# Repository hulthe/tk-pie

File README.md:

# Tk🥧
Alternatively: **tk-pie**, or **Test Keyboard Please IgnorE**.
A split keyboard design and firmware.

## Directory

### `/lib`
A rust library, and the bulk of the keyboard firmware implementation.
Written using the Embassy framework.

### `/left` and `/right`
Rust binaries, one for each half of the split keyboard.
Most of the actual logic is implemented in `/lib`.

### `/schematic`
KiCad schematics of the keyboard PCBs.

### `/case`
3d-printable files of the keyboard case and related plastics.

### `/editor`
A graphical program for configuring the keyboard layout. Work in progress.

## Firmware development

Required tools:
- Rust
- `probe-rs` for flashing the firmware. Follow instructions at https://probe.rs/
- [`flip-link`](https://github.com/knurling-rs/flip-link/)
- A debug probe of some kind, I recommend a [Pitaya-Link](https://github.com/makerdiary/pitaya-link)

To flash:
- plug in the probe,
- `cd` into either `left` or `right`
- `cargo run`

### Running tests
The keyboad library comes with some unit tests:
```
cargo test -p tk-pie --target x86_64-unknown-linux-gnu
```

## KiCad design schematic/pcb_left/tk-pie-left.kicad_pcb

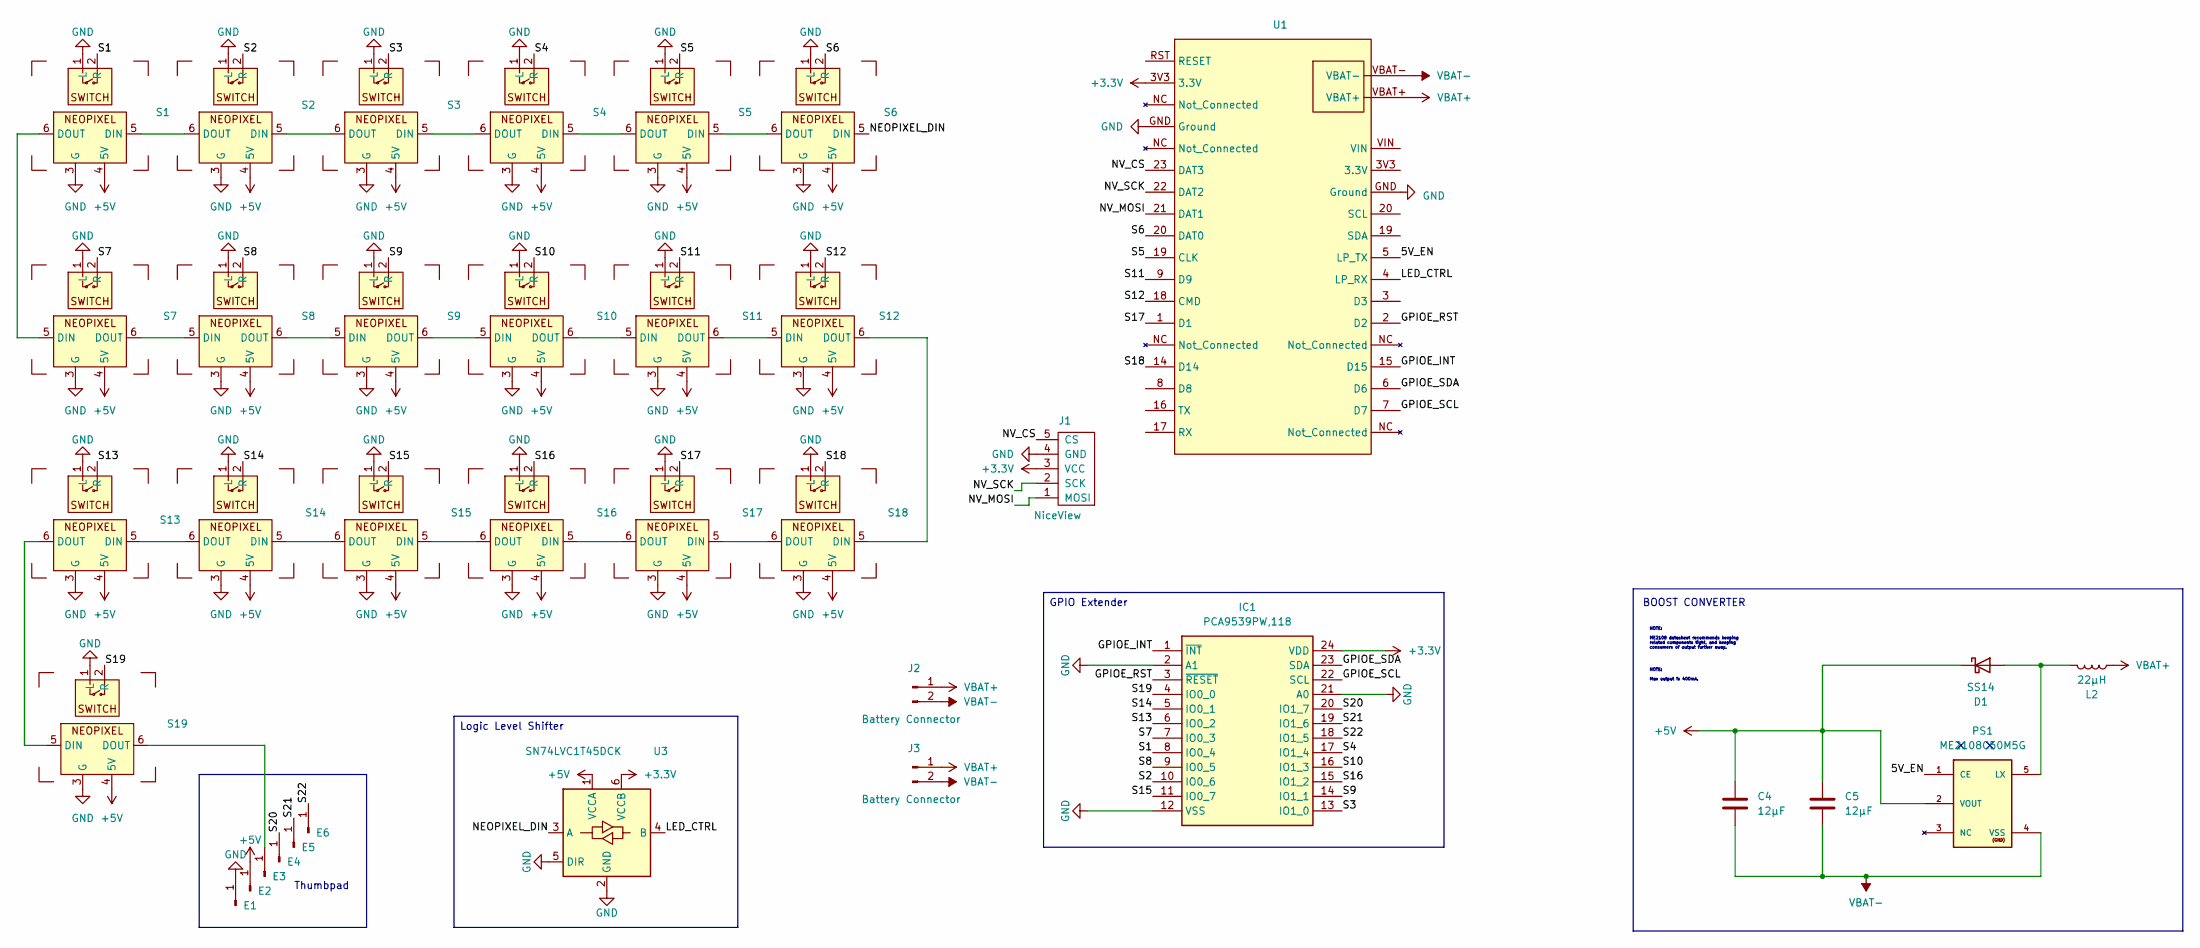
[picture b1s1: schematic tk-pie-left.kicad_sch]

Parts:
C4, C5: 12µF; C_1210_3225Metric_Pad1.33x2.70mm_HandSolder
D1: SS14; D_SMA
E1, E2, E3, E4, E5, E6: Conn_01x01_Pin; Pin0.9mm
IC1: PCA9539PW,118; SOP65P640X110-24N; Manufacturer_Part_Number PCA9539PW,118; Mouser Part Number 771-PCA9539PW-T
J1: NiceView; Nice!View Header
J2, J3: Battery Connector; JST_PH_S2B-PH-SM4-TB_1x02-1MP_P2.00mm_Horizontal
L2: 22µH; L_Cenker_CKCS5040
PS1: ME2108C50M5G; SOT-23-5
S1, S4, S5, S6, S13: MX_SW_SOCKET_LED
S2, S3, S14, S15, S16, S17, S18: MX_SW_SOCKET_LED
S7, S8, S9, S10, S11, S12, S19: MX_SW_SOCKET_RGB_REV; MX_SW_SOCKET_LED_REV
U1: DFR1075
U3: SN74LVC1T45DCK; SOT-363_SC-70-6_Handsoldering

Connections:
+3.3V: IC1.24 (VDD), J1.3 (VCC), U1.3V3 (3.3V), U3.6 (VCCB)
+5V: C4.1, C5.2, D1.1 (K), E2.1, PS1.2 (VOUT), S1.4 (5V), S2.4 (5V), S3.4 (5V), S4.4 (5V), S5.4 (5V), S6.4 (5V), S7.4 (5V), S8.4 (5V), S9.4 (5V), S10.4 (5V), S11.4 (5V), S12.4 (5V), S13.4 (5V), S14.4 (5V), S15.4 (5V), S16.4 (5V), S17.4 (5V), S18.4 (5V), S19.4 (5V), U3.1 (VCCA)
/5V_EN: PS1.1 (CE), U1.5 (LP_TX)
/ NV_CS: J1.5 (CS), U1.23 (DAT3)
/GPIOE_INT: IC1.1 (~INT), U1.15 (D15)
/GPIOE_RST: IC1.3 (~RESET), U1.2 (D2)
/GPIOE_SCL: IC1.22 (SCL), U1.7 (D7)
/GPIOE_SDA: IC1.23 (SDA), U1.6 (D6)
/LED_CTRL: U1.4 (LP_RX), U3.4 (B)
/NEOPIXEL_DIN: S6.5 (DIN), U3.3 (A)
/NV_MOSI: J1.1 (MOSI), U1.21 (DAT1)
/NV_SCK: J1.2 (SCK), U1.22 (DAT2)
/S1: IC1.8 (IO0_4), S1.2 (R)
/S2: IC1.10 (IO0_6), S2.2 (R)
/S3: IC1.13 (IO1_0), S3.2 (R)
/S4: IC1.17 (IO1_4), S4.2 (R)
/S5: S5.2 (R), U1.19 (CLK)
/S6: S6.2 (R), U1.20 (DAT0)
/S7: IC1.7 (IO0_3), S7.2 (R)
/S8: IC1.9 (IO0_5), S8.2 (R)
/S9: IC1.14 (IO1_1), S9.2 (R)
/S10: IC1.16 (IO1_3), S10.2 (R)
/S11: S11.2 (R), U1.9 (D9)
/S12: S12.2 (R), U1.18 (CMD)
/S13: IC1.6 (IO0_2), S13.2 (R)
/S14: IC1.5 (IO0_1), S14.2 (R)
/S15: IC1.11 (IO0_7), S15.2 (R)
/S16: IC1.15 (IO1_2), S16.2 (R)
/S17: S17.2 (R), U1.1 (D1)
/S18: S18.2 (R), U1.14 (D14)
/S19: IC1.4 (IO0_0), S19.2 (R)
/S20: E4.1, IC1.20 (IO1_7)
/S21: E5.1, IC1.19 (IO1_6)
/S22: E6.1, IC1.18 (IO1_5)
GND: E1.1, IC1.2 (A1), IC1.12 (VSS), IC1.21 (A0), J1.4 (GND), S1.1 (L), S1.3 (G), S2.1 (L), S2.3 (G), S3.1 (L), S3.3 (G), S4.1 (L), S4.3 (G), S5.1 (L), S5.3 (G), S6.1 (L), S6.3 (G), S7.1 (L), S7.3 (G), S8.1 (L), S8.3 (G), S9.1 (L), S9.3 (G), S10.1 (L), S10.3 (G), S11.1 (L), S11.3 (G), S12.1 (L), S12.3 (G), S13.1 (L), S13.3 (G), S14.1 (L), S14.3 (G), S15.1 (L), S15.3 (G), S16.1 (L), S16.3 (G), S17.1 (L), S17.3 (G), S18.1 (L), S18.3 (G), S19.1 (L), S19.3 (G), U1.GND (Ground), U3.2 (GND), U3.5 (DIR)
unnamed: D1.2 (A), L2.2, PS1.5 (LX)
unnamed: E3.1, S19.6 (DOUT)
unnamed: S1.5 (DIN), S2.6 (DOUT)
unnamed: S1.6 (DOUT), S7.5 (DIN)
unnamed: S2.5 (DIN), S3.6 (DOUT)
unnamed: S3.5 (DIN), S4.6 (DOUT)
unnamed: S4.5 (DIN), S5.6 (DOUT)
unnamed: S5.5 (DIN), S6.6 (DOUT)
unnamed: S7.6 (DOUT), S8.5 (DIN)
unnamed: S8.6 (DOUT), S9.5 (DIN)
unnamed: S9.6 (DOUT), S10.5 (DIN)
unnamed: S10.6 (DOUT), S11.5 (DIN)
unnamed: S11.6 (DOUT), S12.5 (DIN)
unnamed: S12.6 (DOUT), S18.5 (DIN)
unnamed: S13.5 (DIN), S14.6 (DOUT)
unnamed: S13.6 (DOUT), S19.5 (DIN)
unnamed: S14.5 (DIN), S15.6 (DOUT)
unnamed: S15.5 (DIN), S16.6 (DOUT)
unnamed: S16.5 (DIN), S17.6 (DOUT)
unnamed: S17.5 (DIN), S18.6 (DOUT)
VBAT+: J2.1, J3.1, L2.1, U1.VBAT+
VBAT-: C4.2, C5.1, J2.2, J3.2, PS1.4 (VSS), U1.VBAT-

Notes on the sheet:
NOTE: Max output is 400mA.
NOTE: ME2108 datasheet recommends keeping related components tight, and keeping consumers of output further away.
Thumbpad
GPIO Extender
BOOST CONVERTER
Logic Level Shifter

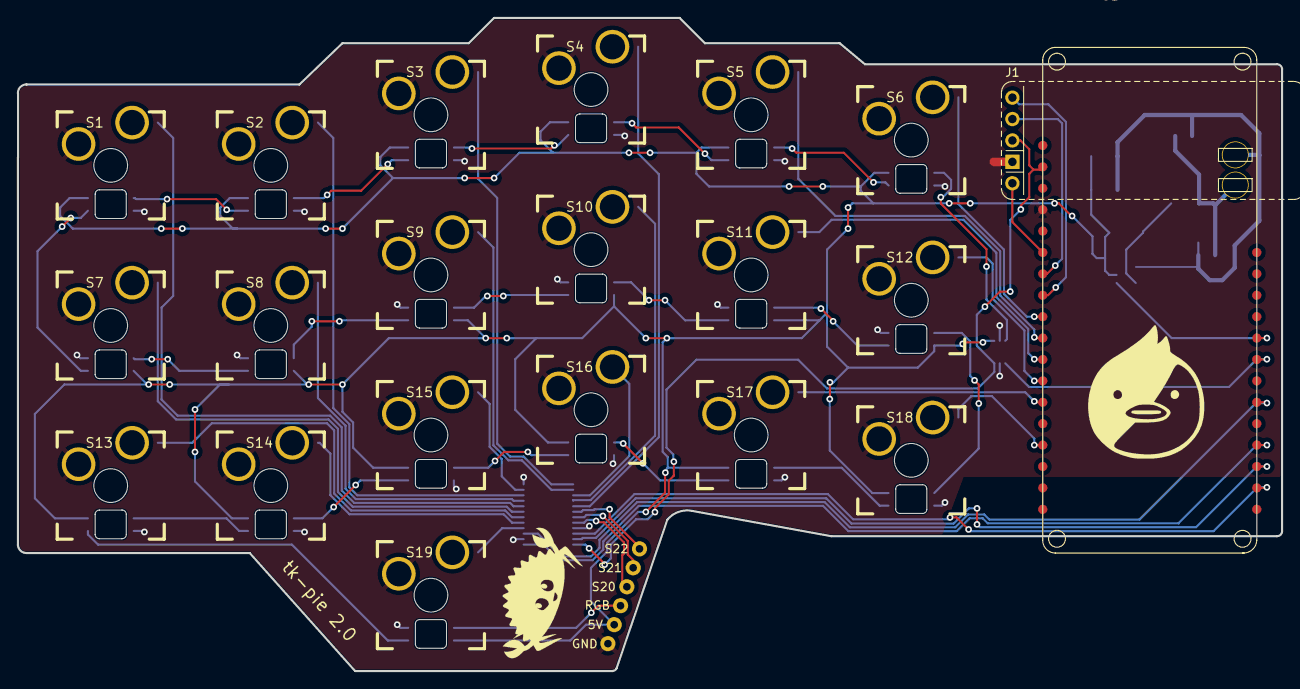
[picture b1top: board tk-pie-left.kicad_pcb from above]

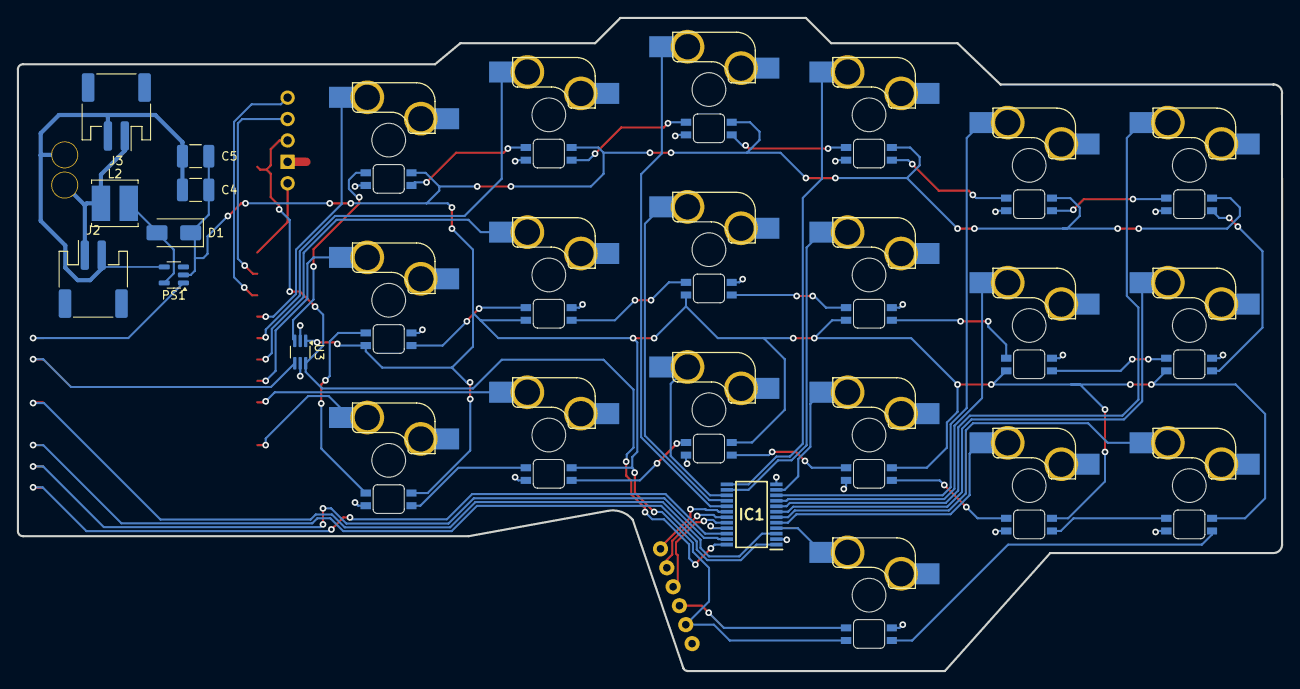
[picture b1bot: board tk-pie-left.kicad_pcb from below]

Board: 2 copper layers, 150.0 x 77.5 mm, 36 parts (9 on the bottom side), 57 nets.

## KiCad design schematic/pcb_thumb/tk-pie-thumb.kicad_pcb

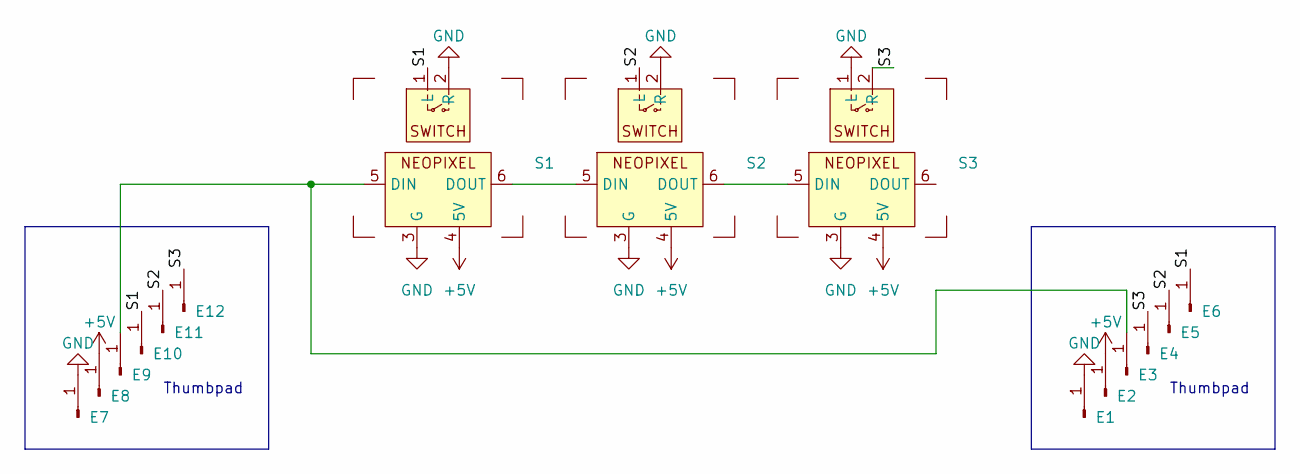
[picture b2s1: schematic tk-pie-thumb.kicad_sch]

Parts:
E1, E2, E3, E4, E5, E6, E7, E8, E9, E10, E11, E12: Conn_01x01_Pin; Pin0.9mm
S1, S2, S3: MX_SW_SOCKET_LED_REV

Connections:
+5V: E2.1, E8.1, S1.4 (5V), S2.4 (5V), S3.4 (5V)
/S1: E6.1, E10.1, S1.1 (L)
/S2: E5.1, E11.1, S2.1 (L)
/S3: E4.1, E12.1, S3.2 (R)
GND: E1.1, E7.1, S1.2 (R), S1.3 (G), S2.2 (R), S2.3 (G), S3.1 (L), S3.3 (G)
unnamed: E3.1, E9.1, S1.5 (DIN)
unnamed: S1.6 (DOUT), S2.5 (DIN)
unnamed: S2.6 (DOUT), S3.5 (DIN)

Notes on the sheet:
Thumbpad

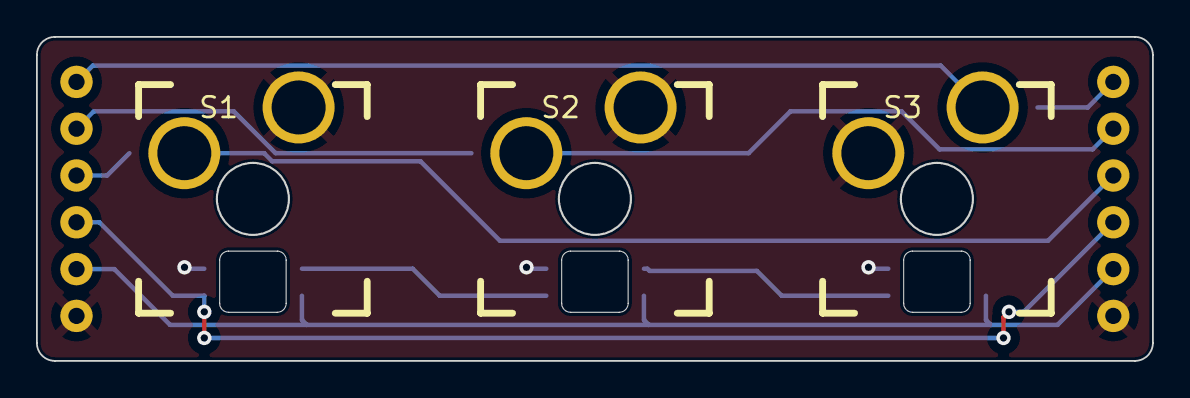
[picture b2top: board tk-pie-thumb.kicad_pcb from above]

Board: 2 copper layers, 62.0 x 18.0 mm, 15 parts (0 on the bottom side), 8 nets.

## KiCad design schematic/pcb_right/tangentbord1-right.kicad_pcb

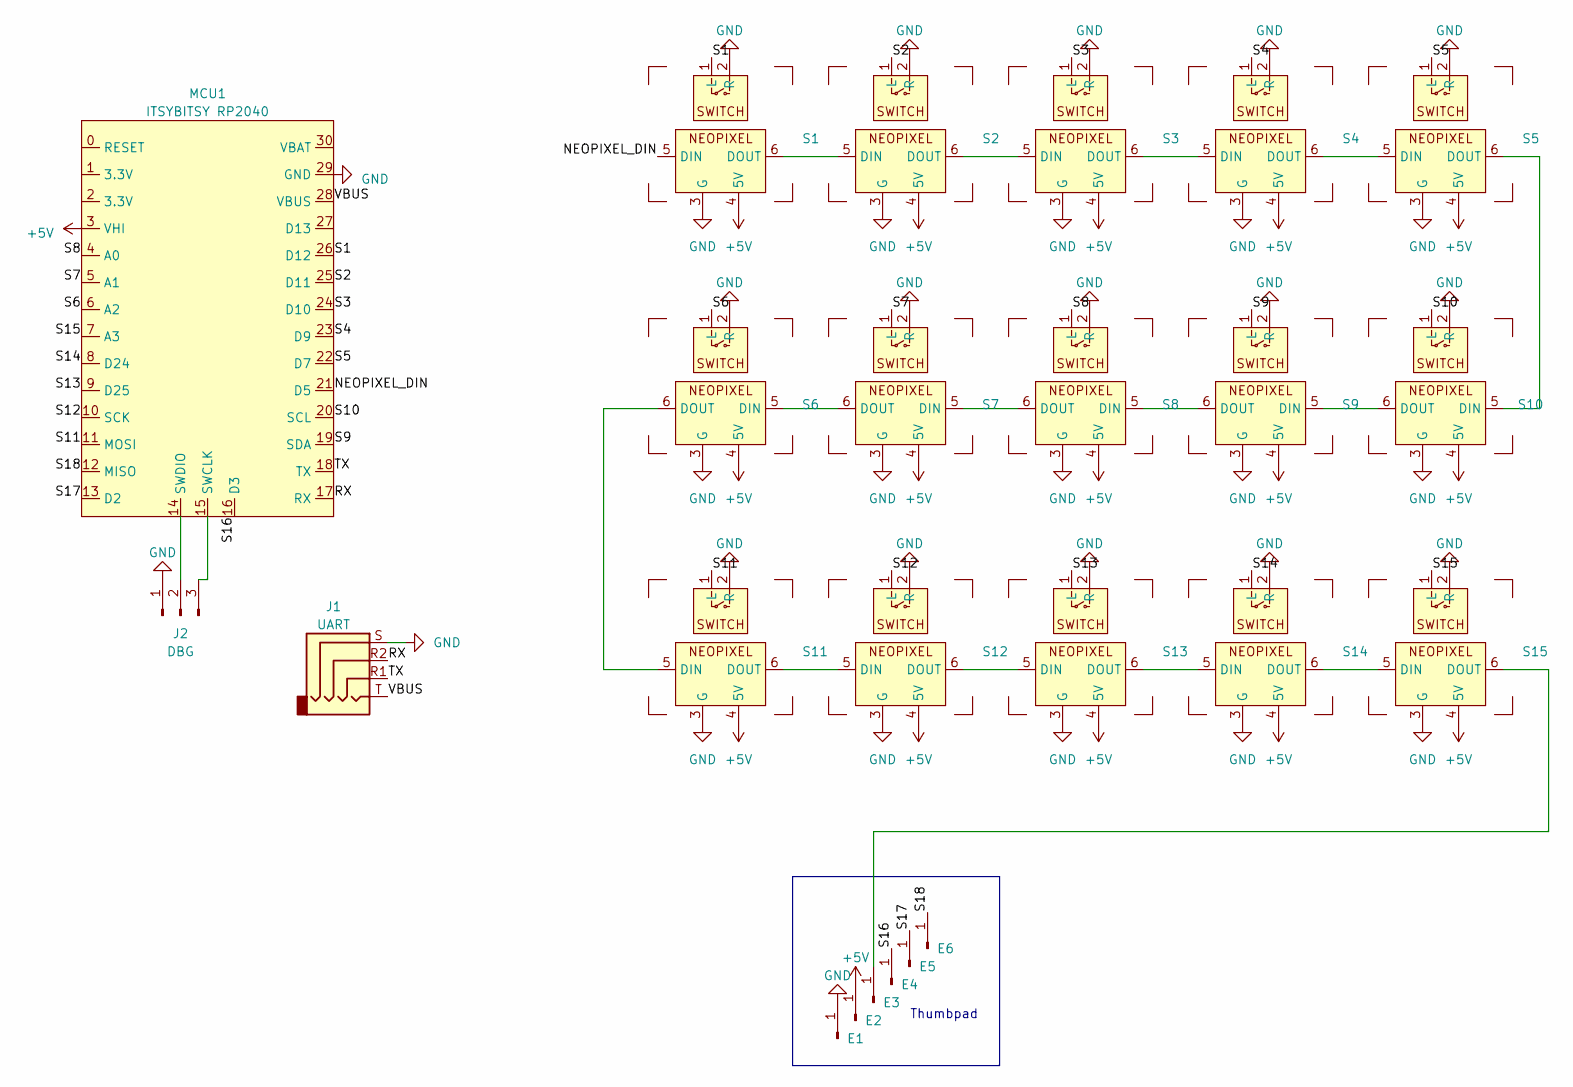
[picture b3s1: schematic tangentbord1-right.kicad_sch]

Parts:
E1, E2, E3, E4, E5, E6: Conn_01x01_Pin; Pin0.9mm
J1: UART; Jack_3.5mm_KoreanHropartsElec_PJ-320D-4A_Horizontal
J2: DBG; PinSocket_1x03_P2.54mm_Vertical
MCU1: ITSYBITSY RP2040; ITSYBITSY BREAKOUT
S1, S2, S11, S12, S13, S14, S15: MX_SW_SOCKET_LED_REV
S3, S4, S5: MX_SW_SOCKET_LED; MX_SW_SOCKET_LED_REV
S6, S7, S8, S9, S10: MX_SW_SOCKET_RGB_REV; MX_SW_SOCKET_LED

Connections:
+5V: E2.1, MCU1.3 (VHI), S1.4 (5V), S2.4 (5V), S3.4 (5V), S4.4 (5V), S5.4 (5V), S6.4 (5V), S7.4 (5V), S8.4 (5V), S9.4 (5V), S10.4 (5V), S11.4 (5V), S12.4 (5V), S13.4 (5V), S14.4 (5V), S15.4 (5V)
/NEOPIXEL_DIN: MCU1.21 (D5), S1.5 (DIN)
/RX: J1.R2, MCU1.17 (RX)
/S1: MCU1.26 (D12), S1.1 (L)
/S2: MCU1.25 (D11), S2.1 (L)
/S3: MCU1.24 (D10), S3.1 (L)
/S4: MCU1.23 (D9), S4.1 (L)
/S5: MCU1.22 (D7), S5.1 (L)
/S6: MCU1.6 (A2), S6.1 (L)
/S7: MCU1.5 (A1), S7.1 (L)
/S8: MCU1.4 (A0), S8.1 (L)
/S9: MCU1.19 (SDA), S9.1 (L)
/S10: MCU1.20 (SCL), S10.1 (L)
/S11: MCU1.11 (MOSI), S11.1 (L)
/S12: MCU1.10 (SCK), S12.1 (L)
/S13: MCU1.9 (D25), S13.1 (L)
/S14: MCU1.8 (D24), S14.1 (L)
/S15: MCU1.7 (A3), S15.1 (L)
/S16: E4.1, MCU1.16 (D3)
/S17: E5.1, MCU1.13 (D2)
/S18: E6.1, MCU1.12 (MISO)
/TX: J1.R1, MCU1.18 (TX)
/VBUS: J1.T, MCU1.28 (VBUS)
GND: E1.1, J1.S, J2.1, MCU1.29 (GND), S1.2 (R), S1.3 (G), S2.2 (R), S2.3 (G), S3.2 (R), S3.3 (G), S4.2 (R), S4.3 (G), S5.2 (R), S5.3 (G), S6.2 (R), S6.3 (G), S7.2 (R), S7.3 (G), S8.2 (R), S8.3 (G), S9.2 (R), S9.3 (G), S10.2 (R), S10.3 (G), S11.2 (R), S11.3 (G), S12.2 (R), S12.3 (G), S13.2 (R), S13.3 (G), S14.2 (R), S14.3 (G), S15.2 (R), S15.3 (G)
unnamed: E3.1, S15.6 (DOUT)
unnamed: J2.2, MCU1.14 (SWDIO)
unnamed: J2.3, MCU1.15 (SWCLK)
unnamed: S1.6 (DOUT), S2.5 (DIN)
unnamed: S2.6 (DOUT), S3.5 (DIN)
unnamed: S3.6 (DOUT), S4.5 (DIN)
unnamed: S4.6 (DOUT), S5.5 (DIN)
unnamed: S6.5 (DIN), S7.6 (DOUT)
unnamed: S7.5 (DIN), S8.6 (DOUT)
unnamed: S8.5 (DIN), S9.6 (DOUT)
unnamed: S5.6 (DOUT), S10.5 (DIN)
unnamed: S9.5 (DIN), S10.6 (DOUT)
unnamed: S6.6 (DOUT), S11.5 (DIN)
unnamed: S11.6 (DOUT), S12.5 (DIN)
unnamed: S12.6 (DOUT), S13.5 (DIN)
unnamed: S13.6 (DOUT), S14.5 (DIN)
unnamed: S14.6 (DOUT), S15.5 (DIN)

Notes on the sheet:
Thumbpad

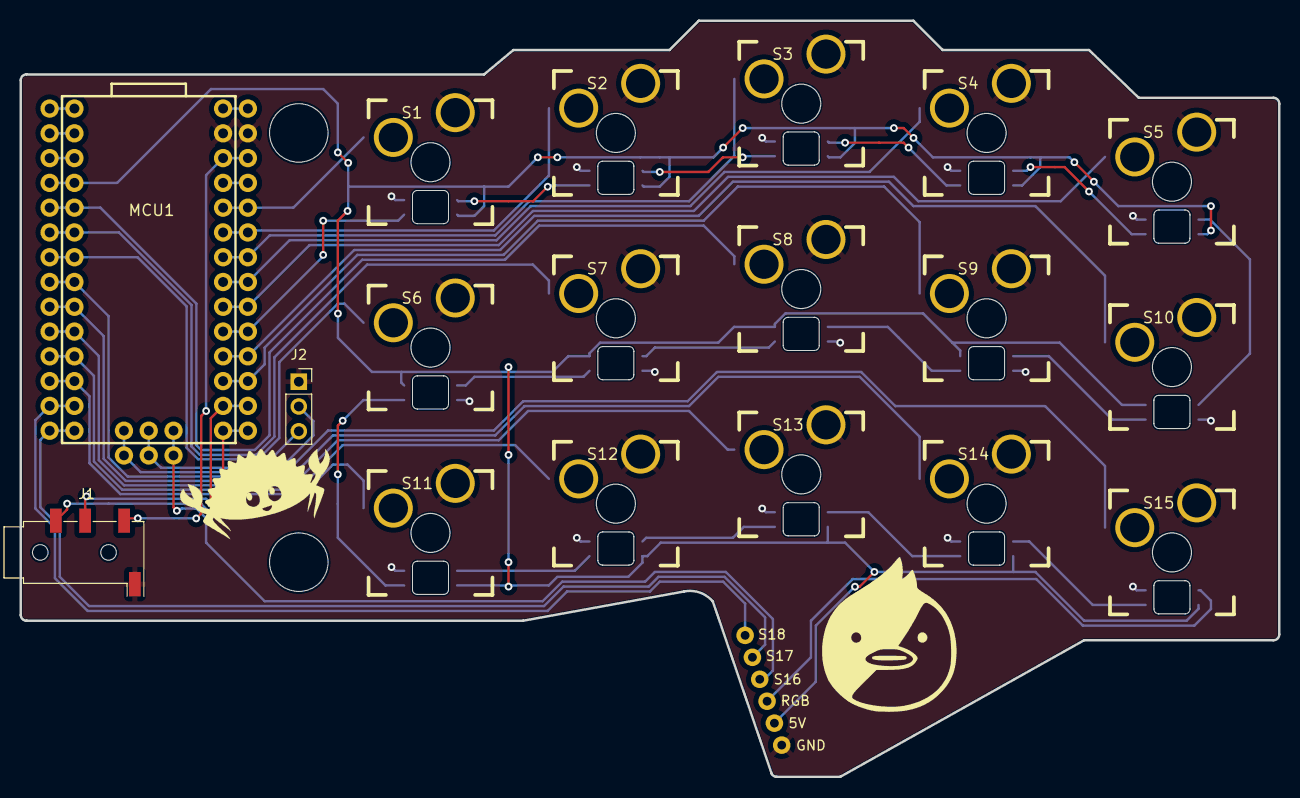
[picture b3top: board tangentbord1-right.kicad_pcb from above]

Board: 2 copper layers, 129.0 x 77.5 mm, 24 parts (0 on the bottom side), 41 nets.

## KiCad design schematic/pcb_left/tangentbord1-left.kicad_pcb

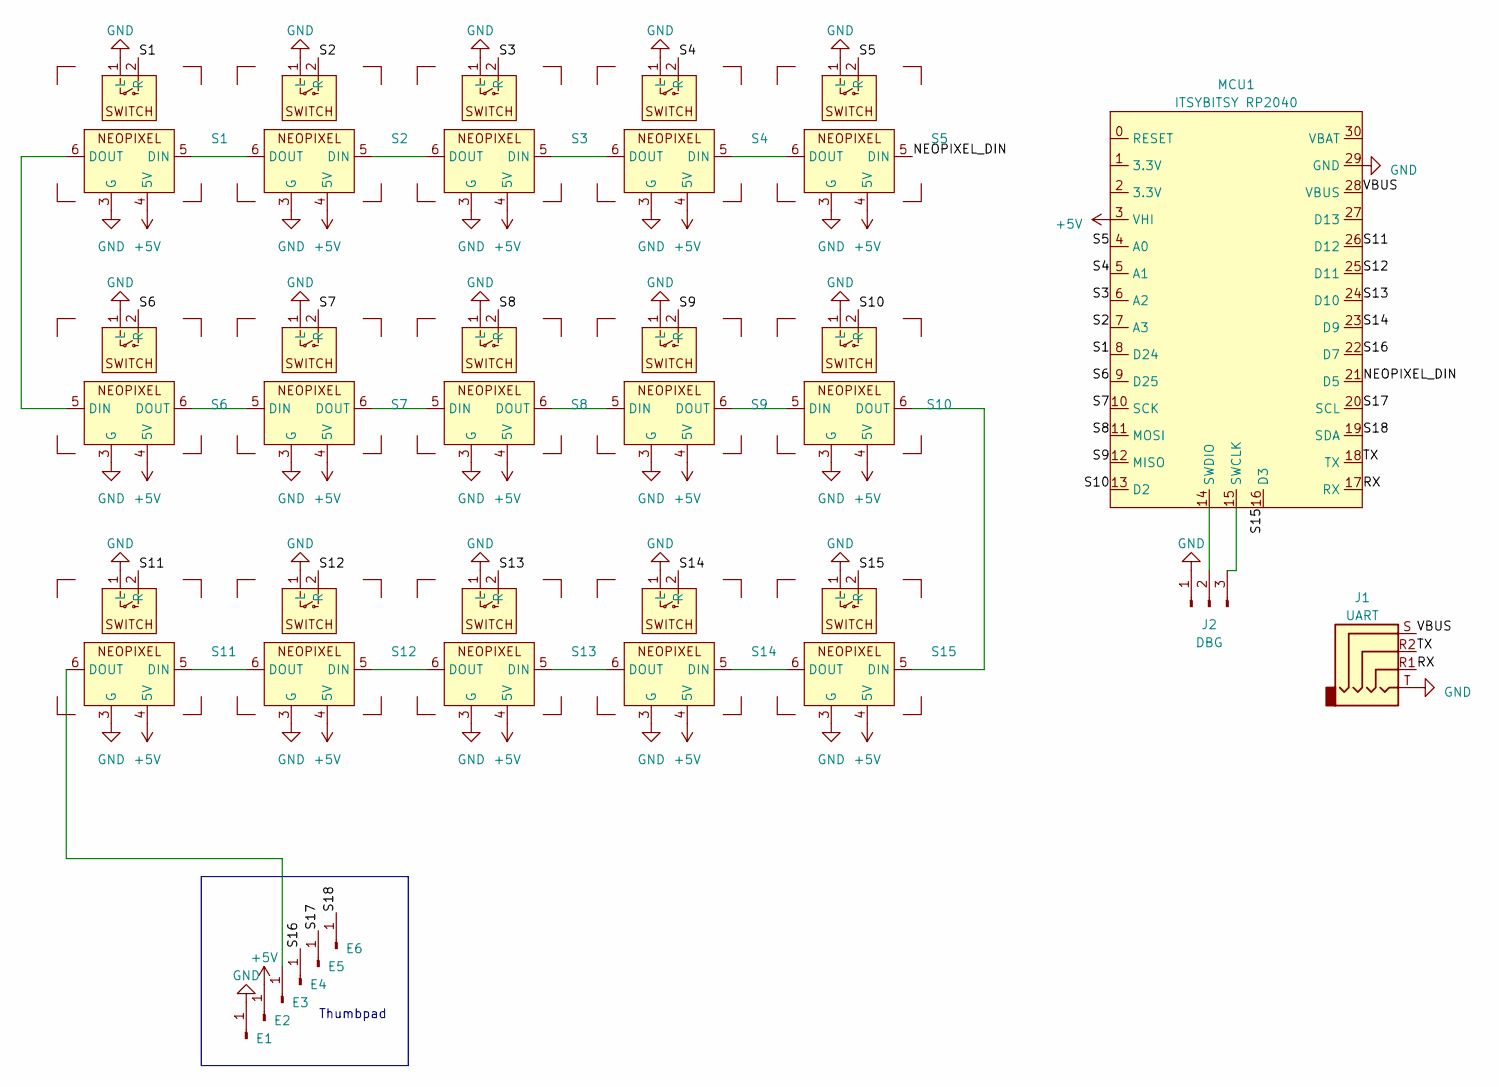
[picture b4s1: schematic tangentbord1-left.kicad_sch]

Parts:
E1, E2, E3, E4, E5, E6: Conn_01x01_Pin; Pin_D0.9mm_L10.0mm_W2.4mm_FlatFork
J1: UART; Jack_3.5mm_KoreanHropartsElec_PJ-320D-4A_Horizontal
J2: DBG; PinSocket_1x03_P2.54mm_Vertical
MCU1: ITSYBITSY RP2040; ITSYBITSY BREAKOUT
S1, S2, S11, S12, S13, S14, S15: MX_SW_SOCKET_LED
S3, S4, S5: MX_SW_SOCKET_LED
S6, S7, S8, S9, S10: MX_SW_SOCKET_RGB_REV; MX_SW_SOCKET_LED_REV

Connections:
+5V: E2.1, MCU1.3 (VHI), S1.4 (5V), S2.4 (5V), S3.4 (5V), S4.4 (5V), S5.4 (5V), S6.4 (5V), S7.4 (5V), S8.4 (5V), S9.4 (5V), S10.4 (5V), S11.4 (5V), S12.4 (5V), S13.4 (5V), S14.4 (5V), S15.4 (5V)
/NEOPIXEL_DIN: MCU1.21 (D5), S5.5 (DIN)
/RX: J1.R1, MCU1.17 (RX)
/S1: MCU1.8 (D24), S1.2 (R)
/S2: MCU1.7 (A3), S2.2 (R)
/S3: MCU1.6 (A2), S3.2 (R)
/S4: MCU1.5 (A1), S4.2 (R)
/S5: MCU1.4 (A0), S5.2 (R)
/S6: MCU1.9 (D25), S6.2 (R)
/S7: MCU1.10 (SCK), S7.2 (R)
/S8: MCU1.11 (MOSI), S8.2 (R)
/S9: MCU1.12 (MISO), S9.2 (R)
/S10: MCU1.13 (D2), S10.2 (R)
/S11: MCU1.26 (D12), S11.2 (R)
/S12: MCU1.25 (D11), S12.2 (R)
/S13: MCU1.24 (D10), S13.2 (R)
/S14: MCU1.23 (D9), S14.2 (R)
/S15: MCU1.16 (D3), S15.2 (R)
/S16: E4.1, MCU1.22 (D7)
/S17: E5.1, MCU1.20 (SCL)
/S18: E6.1, MCU1.19 (SDA)
/TX: J1.R2, MCU1.18 (TX)
unnamed: E3.1, S11.6 (DOUT)
unnamed: J2.2, MCU1.14 (SWDIO)
unnamed: J2.3, MCU1.15 (SWCLK)
unnamed: S1.5 (DIN), S2.6 (DOUT)
unnamed: S1.6 (DOUT), S6.5 (DIN)
unnamed: S2.5 (DIN), S3.6 (DOUT)
unnamed: S3.5 (DIN), S4.6 (DOUT)
unnamed: S4.5 (DIN), S5.6 (DOUT)
unnamed: S6.6 (DOUT), S7.5 (DIN)
unnamed: S7.6 (DOUT), S8.5 (DIN)
unnamed: S8.6 (DOUT), S9.5 (DIN)
unnamed: S9.6 (DOUT), S10.5 (DIN)
unnamed: S10.6 (DOUT), S15.5 (DIN)
unnamed: S11.5 (DIN), S12.6 (DOUT)
unnamed: S12.5 (DIN), S13.6 (DOUT)
unnamed: S13.5 (DIN), S14.6 (DOUT)
unnamed: S14.5 (DIN), S15.6 (DOUT)

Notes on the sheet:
Thumbpad

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
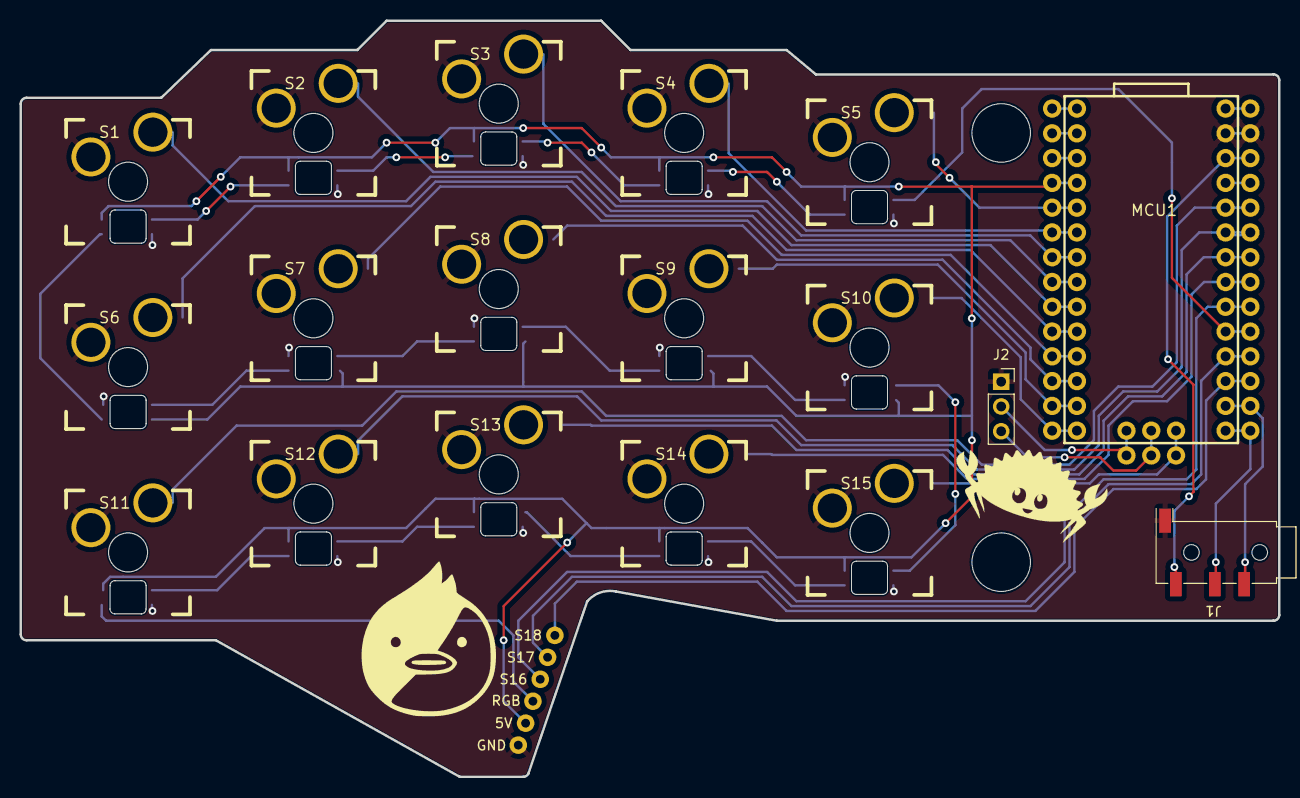
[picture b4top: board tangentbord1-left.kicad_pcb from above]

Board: 2 copper layers, 129.0 x 77.5 mm, 24 parts (0 on the bottom side), 41 nets.

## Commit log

2023-03-04 Initial Commit - Blinky
2023-03-05 Get a dummy keyboard working
2023-03-13 Get most basics working
    - Control (at least) 1 neopixel
    - Add basic blinky panic handler
    - Support N-key rollover
    - Test GPIO pins
2023-03-16 Improve ws2812 api
2023-03-17 Move away from matrix-based key layout
2023-03-17 Split firmware inte left.rs and right.rs.
2023-03-18 Remove auto-generated layout files
2023-03-19 Implement modifiers and modtap
2023-04-05 Add PCB schematic
2023-04-05 Add kicad .gitignore
2023-04-16 Tweak left PCB, add right & thumb PCB
2023-04-16 Add export files to kicad gitignore
2023-04-16 Swap RX/TX on pcb_right
2023-04-26 Add serial-logs script
2023-04-26 Make keys light up when pressed
2023-05-08 Fix right.rs
2023-05-09 Add communication between keyboard halves
2023-05-09 Add light to layer switch key
2023-05-14 Refactor light handling to use event messages
2023-05-15 Add idle animation
2023-05-15 Update layout
2023-05-20 Update dependencies
2023-05-21 Add RTT logging
2023-05-21 Use postcard to serialize uart messages
2023-05-21 Add fado out effect to button presses
2023-05-29 Add uart Header struct
2023-06-12 stuff
2023-07-14 Add basic swich debouncing.
2023-07-21 Switch to layer matrix instead of layer list
2023-08-28 Remove patch
2023-08-28 Increase debounce threshold
2023-08-28 Decrease idle animation brightness
2023-12-16 Update deps
2023-12-16 Refactor keyboard timing tests
2023-12-16 Fix the bug that has been bugging me for months
    Finally got the little shit :D
2023-12-19 Tweak brightness
2023-12-20 Some cleanup
2024-02-04 Add naive Compose button impl
2024-02-04 Flash LEDs on USB events
2024-02-08 Rename split_array
2024-02-10 Refactor keyboarg lights
2024-02-16 Refactor idle animation
2024-05-29 Swap super and alt keys
2024-05-29 Remove old todos
2024-05-29 Remove deprecated neopixel files
2024-06-23 Get Compose keys working with proper shifting
2024-07-03 Remap layer 2,0 slightly.
    Add arrow keys and move F-keys
2024-07-07 Add 3d-files for case
2024-07-14 Add a README
2024-07-14 Make `cargo check` work in the top directory
2024-07-14 Remove old broken `run` script
2024-07-16 Bump deps
2024-07-16 Edit mode & refactor GUI
2024-07-16 Refactor serial portion of sidepanel
2024-07-16 Rename project to tk-pie
2024-07-17 Update comments to be accurate?
2024-07-17 Update default layer to match current types
2024-07-17 Support multiple layouts
2024-07-17 Fix warnings
2024-07-18 Add agave mono nerd font
2024-07-18 Implement display for key
2024-07-18 Update how buttons are displayed
2024-07-18 Default to agave nerd font
2024-07-31 Add DFR1075 footprint
2024-07-31 Add DFR1075 symbol
2024-08-11 Began adding new keys & new MCU
2024-08-11 Initial left PCB v2 updates
    Some todos remain here:
    - Remove the old MCU (left as reference atm)
    - Add GPIO expander
    - Setup pin numbering (considering potential pins for
    battery/gpio-expander/led-off-switch/debug)
2024-08-11 Remove interloping extra button
    Don't know why they were there but now they are dead and no-one will be
    the wiser...
2024-08-11 Replicate left side update to right pcb
2024-08-12 Finish merge with hulthe
2024-08-14 Began assigning pins for left PCB
2024-08-15 Update schematic
2024-08-15 Fix DRF symbol->footprint link
2024-08-15 gitignore .lck
2024-08-15 Update/fix ME2108 schematic
2024-08-15 Tweak DF schematic pins
2024-08-15 Add Nice!View header symbol
2024-08-21 rust-toolchain: Add rust-analyzer component
2024-08-21 Remove arch-cfg for lib::lights module
2024-08-21 Add component-cycle lights shader
2024-08-24 Fix keypress_handler tests and add one more
2024-08-24 readme: Add note on running unit tests
2024-08-24 Fix bug in keypress_handler
2024-08-24 Add footprints for boost circuit
2024-09-07 Make UART communication more robust
2024-09-07 Fix oops
2024-09-07 Add udev rules file
2024-09-09 Add priority executors to run important tasks
2024-10-27 Start wiring up components
2024-11-19 Add logic level shifter to schematic
2025-01-08 Connect ground on left PCB
2025-01-08 Connect neopixels on left pcb
    Also connect missed ground
2025-01-08 Move and connect logic level thingy
2025-01-08 Add better niceview footprint
2025-04-14 Fix some schematic errors
2025-05-20 More schematics
2025-08-15 Copy tk-pie-left to right and auto-flip it
2025-08-15 pcb_right: Fix mcu position
2025-08-15 Move GPIO extender to 3V supply
2025-08-15 RIGHT PCB ???? TRACES VIAS!!!!
2025-08-15 Save Ferris
2025-08-17 schematic: Add workspace project
2025-08-17 pcb_right: Minor PCB improvments.
    - Optimize routing slightly, especially for 3v3 rail.
    - Out of caution: Make sure we don't route any wires on the front layer
    where MCU copper will contact the PCB.
2025-09-24 pcb-left: Add through-holes to vbat pads
2025-09-24 pcb-right: Add through-holes to vbat pads
2025-09-24 [W.I.P]: Added another battery connector
    Also moved around our existing boost circut.
2025-09-28 Slight updates to battery circuits
2025-11-09 pcb-left: Fix battery traces
2025-11-09 pcb-left: Add name and revision
2026-04-19 WIP update dependencies
2026-04-19 wip fix ws2812
2026-04-19 wip fixes
2026-04-19 more fixes
2026-04-19 Made things peri
2026-04-19 Ignore vscode dir
2026-04-19 More peri
2026-04-19 wip more fixes
2026-04-19 Remove peri?
